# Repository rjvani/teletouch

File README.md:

# TeletouchApi

This project was generated with [angular-cli](https://github.com/angular/angular-cli) version 1.0.0-beta.28.3.

## Development server
Run `ng serve` for a dev server. Navigate to `http://localhost:4200/`. The app will automatically reload if you change any of the source files.

## Code scaffolding

Run `ng generate component component-name` to generate a new component. You can also use `ng generate directive/pipe/service/class/module`.

## Build

Run `ng build` to build the project. The build artifacts will be stored in the `dist/` directory. Use the `-prod` flag for a production build.

## Running unit tests

Run `ng test` to execute the unit tests via [Karma](https://karma-runner.github.io).

## Running end-to-end tests

Run `ng e2e` to execute the end-to-end tests via [Protractor](http://www.protractortest.org/).
Before running the tests make sure you are serving the app via `ng serve`.

## Deploying to GitHub Pages

Run `ng github-pages:deploy` to deploy to GitHub Pages.

## Further help

To get more help on the `angular-cli` use `ng help` or go check out the [Angular-CLI README](https://github.com/angular/angular-cli/blob/master/README.md).

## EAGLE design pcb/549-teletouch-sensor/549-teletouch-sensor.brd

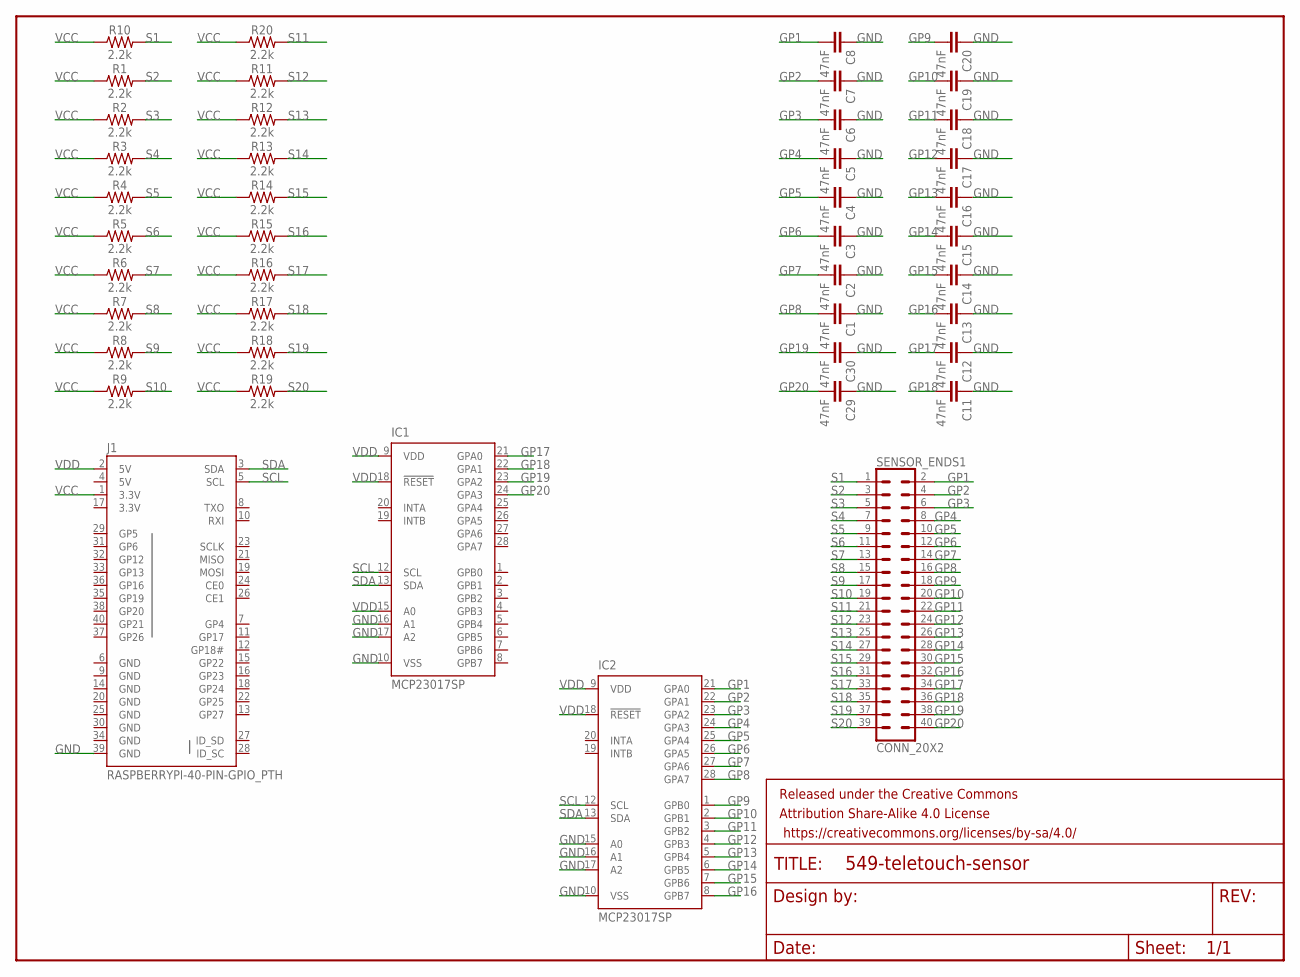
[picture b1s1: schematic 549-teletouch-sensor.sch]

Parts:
C1, C2, C3, C4, C5, C6, C7, C8, C11, C12, C13, C14, C15, C16, C17, C18, C19, C20, C29, C30: 47nF; 0603
FRAME1: FRAME-LETTER; CREATIVE_COMMONS
IC1, IC2: MCP23017SP; DIL28-3
J1: RASPBERRYPI-40-PIN-GPIO_PTH; 2X20_SHROUDED
R1, R2, R3, R4, R5, R6, R7, R8, R9, R10, R11, R12, R13, R14, R15, R16, R17, R18, R19, R20: 2.2k; 0603
SENSOR_ENDS1: CONN_20X2; 2X20

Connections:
3.3V: J1.17 (3.3V)
5V: J1.4 (5V)
GND: C1.1, C2.1, C3.1, C4.1, C5.1, C6.1, C7.1, C8.1, C11.1, C12.1, C13.1, C14.1, C15.1, C16.1, C17.1, C18.1, C19.1, C20.1, C29.1, C30.1, IC1.10 (VSS), IC1.16 (A1), IC1.17 (A2), IC2.10 (VSS), IC2.15 (A0), IC2.16 (A1), IC2.17 (A2), J1.6 (GND), J1.9 (GND), J1.14 (GND), J1.20 (GND), J1.25 (GND), J1.30 (GND), J1.34 (GND), J1.39 (GND)
GP1: C8.2, IC2.21 (GPA0), SENSOR_ENDS1.2
GP2: C7.2, IC2.22 (GPA1), SENSOR_ENDS1.4
GP3: C6.2, IC2.23 (GPA2), SENSOR_ENDS1.6
GP4: C5.2, IC2.24 (GPA3), SENSOR_ENDS1.8
GP5: C4.2, IC2.25 (GPA4), SENSOR_ENDS1.10
GP6: C3.2, IC2.26 (GPA5), SENSOR_ENDS1.12
GP7: C2.2, IC2.27 (GPA6), SENSOR_ENDS1.14
GP8: C1.2, IC2.28 (GPA7), SENSOR_ENDS1.16
GP9: C20.2, IC2.1 (GPB0), SENSOR_ENDS1.18
GP10: C19.2, IC2.2 (GPB1), SENSOR_ENDS1.20
GP11: C18.2, IC2.3 (GPB2), SENSOR_ENDS1.22
GP12: C17.2, IC2.4 (GPB3), SENSOR_ENDS1.24
GP13: C16.2, IC2.5 (GPB4), SENSOR_ENDS1.26
GP14: C15.2, IC2.6 (GPB5), SENSOR_ENDS1.28
GP15: C14.2, IC2.7 (GPB6), SENSOR_ENDS1.30
GP16: C13.2, IC2.8 (GPB7), SENSOR_ENDS1.32
GP17: C12.2, IC1.21 (GPA0), SENSOR_ENDS1.34
GP18: C11.2, IC1.22 (GPA1), SENSOR_ENDS1.36
GP19: C30.2, IC1.23 (GPA2), SENSOR_ENDS1.38
GP20: C29.2, IC1.24 (GPA3), SENSOR_ENDS1.40
S1: R10.2, SENSOR_ENDS1.1
S2: R1.2, SENSOR_ENDS1.3
S3: R2.2, SENSOR_ENDS1.5
S4: R3.2, SENSOR_ENDS1.7
S5: R4.2, SENSOR_ENDS1.9
S6: R5.2, SENSOR_ENDS1.11
S7: R6.2, SENSOR_ENDS1.13
S8: R7.2, SENSOR_ENDS1.15
S9: R8.2, SENSOR_ENDS1.17
S10: R9.2, SENSOR_ENDS1.19
S11: R20.2, SENSOR_ENDS1.21
S12: R11.2, SENSOR_ENDS1.23
S13: R12.2, SENSOR_ENDS1.25
S14: R13.2, SENSOR_ENDS1.27
S15: R14.2, SENSOR_ENDS1.29
S16: R15.2, SENSOR_ENDS1.31
S17: R16.2, SENSOR_ENDS1.33
S18: R17.2, SENSOR_ENDS1.35
S19: R18.2, SENSOR_ENDS1.37
S20: R19.2, SENSOR_ENDS1.39
SCL: IC1.12 (SCL), IC2.12 (SCL), J1.5 (SCL)
SDA: IC1.13 (SDA), IC2.13 (SDA), J1.3 (SDA)
VCC: J1.1 (3.3V), R1.1, R2.1, R3.1, R4.1, R5.1, R6.1, R7.1, R8.1, R9.1, R10.1, R11.1, R12.1, R13.1, R14.1, R15.1, R16.1, R17.1, R18.1, R19.1, R20.1
VDD: IC1.9 (VDD), IC1.15 (A0), IC1.18 (!RESET), IC2.9 (VDD), IC2.18 (!RESET), J1.2 (5V)

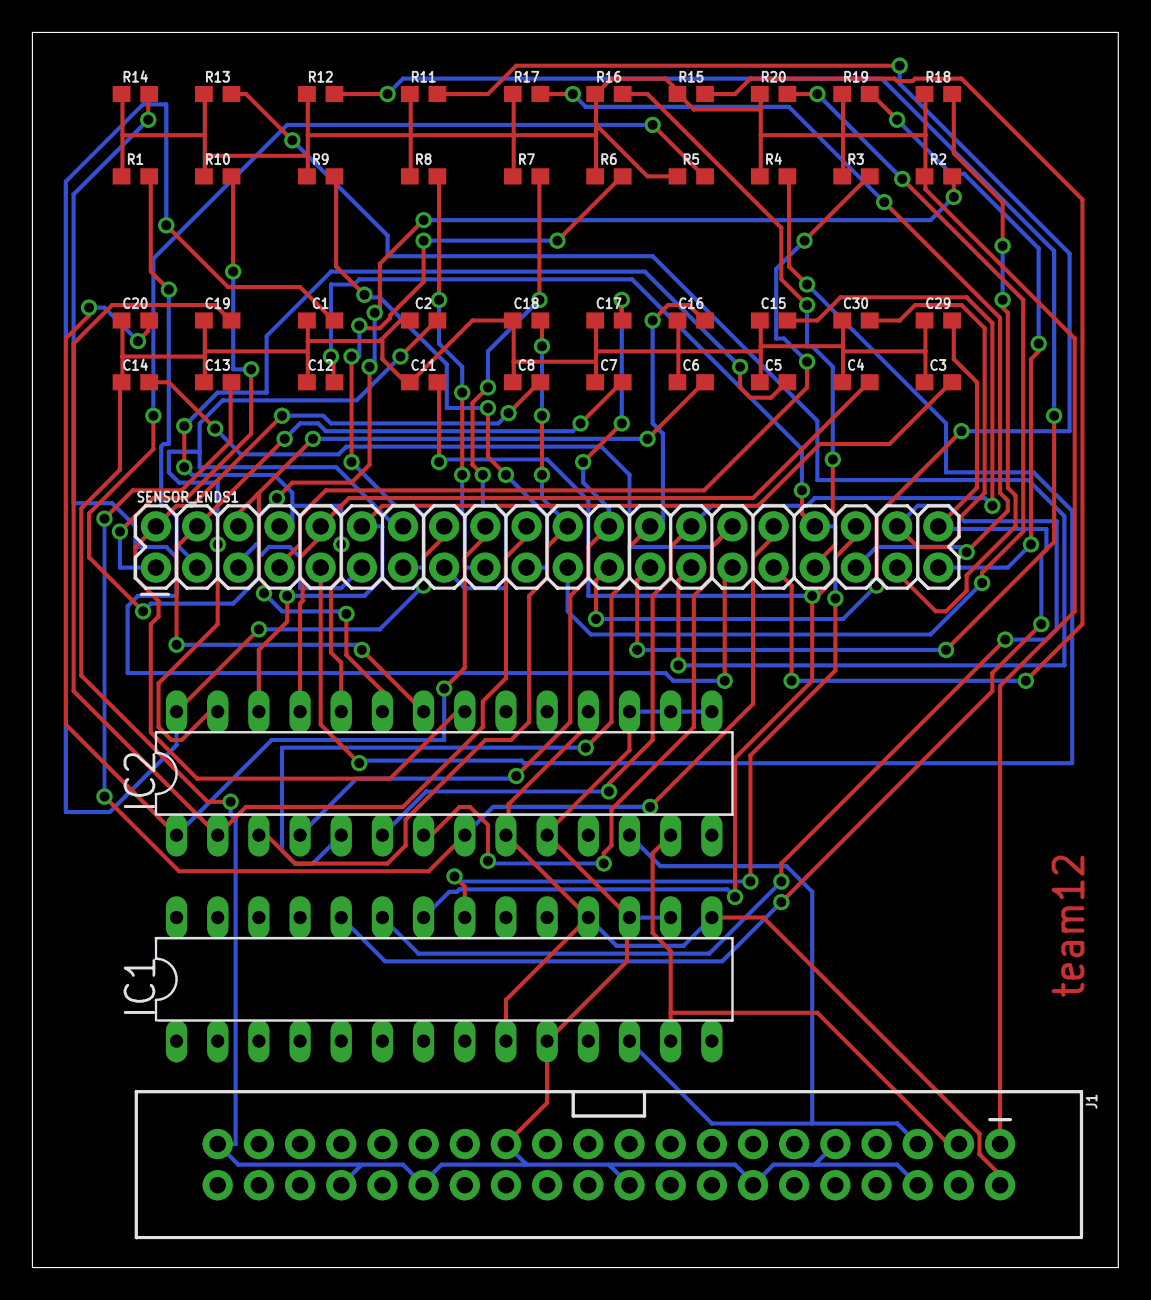
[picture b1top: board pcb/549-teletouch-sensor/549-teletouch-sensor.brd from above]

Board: 2 copper layers, 67.0 x 76.2 mm, 45 parts (0 on the bottom side), 45 nets.

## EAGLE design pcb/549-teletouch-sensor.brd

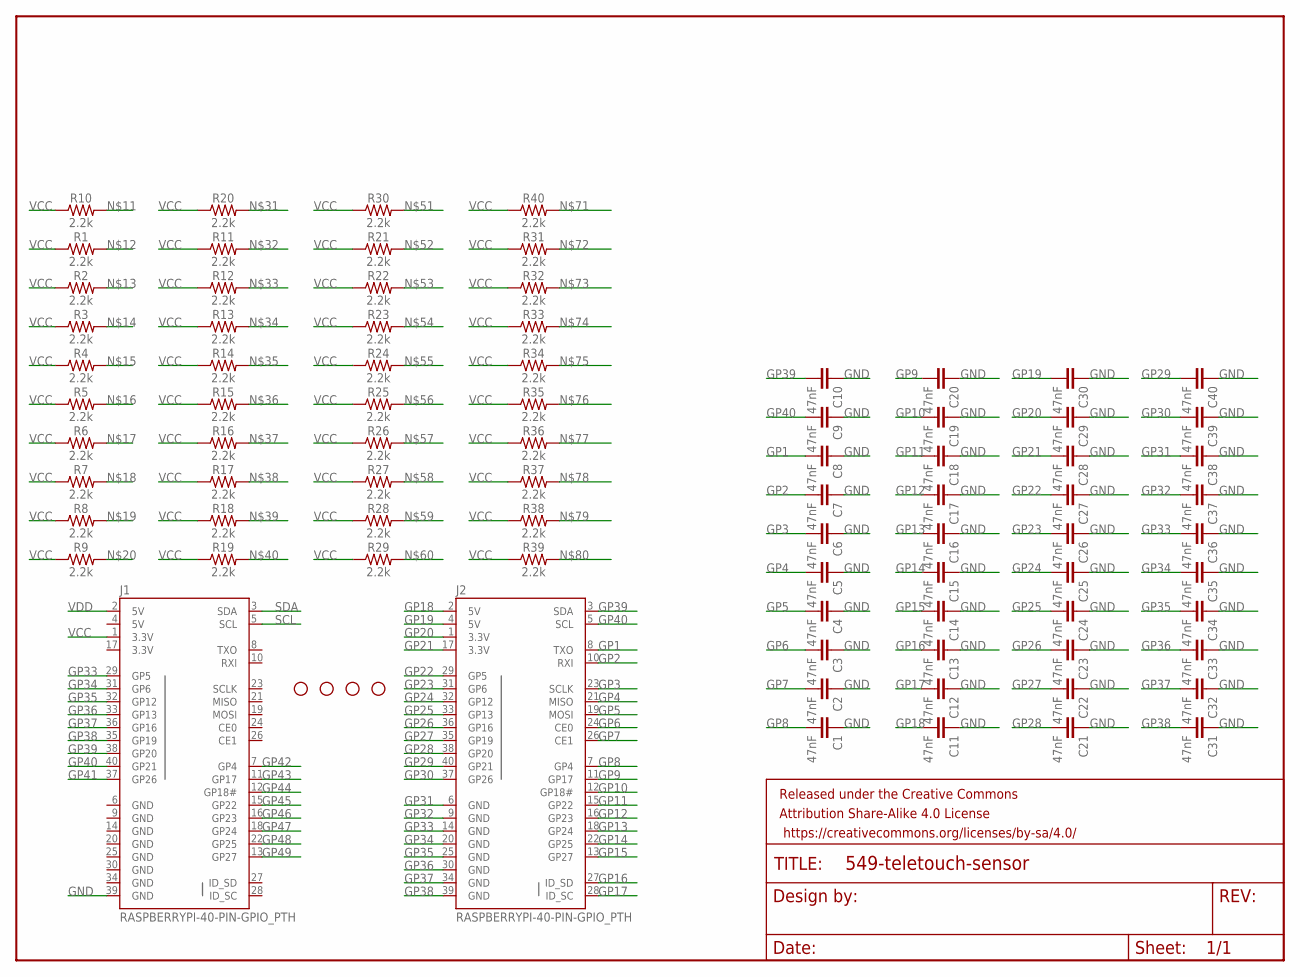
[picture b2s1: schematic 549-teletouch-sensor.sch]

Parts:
C1, C2, C3, C4, C5, C6, C7, C8, C9, C10, C11, C12, C13, C14, C15, C16, C17, C18, C19, C20, C21, C22, C23, C24, C25, C26, C27, C28, C29, C30, C31, C32, C33, C34, C35, C36, C37, C38, C39, C40: 47nF; 0603
FRAME1: FRAME-LETTER; CREATIVE_COMMONS
H1, H2, H3, H4: STAND-OFF
J1, J2: RASPBERRYPI-40-PIN-GPIO_PTH; 2X20_SHROUDED
R1, R2, R3, R4, R5, R6, R7, R8, R9, R10, R11, R12, R13, R14, R15, R16, R17, R18, R19, R20, R21, R22, R23, R24, R25, R26, R27, R28, R29, R30, R31, R32, R33, R34, R35, R36, R37, R38, R39, R40: 2.2k; 0603

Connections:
3.3V: J1.17 (3.3V)
5V: J1.4 (5V)
GND: C1.1, C2.1, C3.1, C4.1, C5.1, C6.1, C7.1, C8.1, C9.1, C10.1, C11.1, C12.1, C13.1, C14.1, C15.1, C16.1, C17.1, C18.1, C19.1, C20.1, C21.1, C22.1, C23.1, C24.1, C25.1, C26.1, C27.1, C28.1, C29.1, C30.1, C31.1, C32.1, C33.1, C34.1, C35.1, C36.1, C37.1, C38.1, C39.1, C40.1, J1.6 (GND), J1.9 (GND), J1.14 (GND), J1.20 (GND), J1.25 (GND), J1.30 (GND), J1.34 (GND), J1.39 (GND)
GP1: C8.2, J2.8 (TXO)
GP2: C7.2, J2.10 (RXI)
GP3: C6.2, J2.23 (SCLK)
GP4: C5.2, J2.21 (MISO)
GP5: C4.2, J2.19 (MOSI)
GP6: C3.2, J2.24 (CE0)
GP7: C2.2, J2.26 (CE1)
GP8: C1.2, J2.7 (GP4)
GP9: C20.2, J2.11 (GP17)
GP10: C19.2, J2.12 (GP18#)
GP11: C18.2, J2.15 (GP22)
GP12: C17.2, J2.16 (GP23)
GP13: C16.2, J2.18 (GP24)
GP14: C15.2, J2.22 (GP25)
GP15: C14.2, J2.13 (GP27)
GP16: C13.2, J2.27 (ID_SD)
GP17: C12.2, J2.28 (ID_SC)
GP18: C11.2, J2.2 (5V)
GP19: C30.2, J2.4 (5V)
GP20: C29.2, J2.1 (3.3V)
GP21: C28.2, J2.17 (3.3V)
GP22: C27.2, J2.29 (GP5)
GP23: C26.2, J2.31 (GP6)
GP24: C25.2, J2.32 (GP12)
GP25: C24.2, J2.33 (GP13)
GP26: C23.2, J2.36 (GP16)
GP27: C22.2, J2.35 (GP19)
GP28: C21.2, J2.38 (GP20)
GP29: C40.2, J2.40 (GP21)
GP30: C39.2, J2.37 (GP26)
GP31: C38.2, J2.6 (GND)
GP32: C37.2, J2.9 (GND)
GP33: C36.2, J1.29 (GP5), J2.14 (GND)
GP34: C35.2, J1.31 (GP6), J2.20 (GND)
GP35: C34.2, J1.32 (GP12), J2.25 (GND)
GP36: C33.2, J1.33 (GP13), J2.30 (GND)
GP37: C32.2, J1.36 (GP16), J2.34 (GND)
GP38: C31.2, J1.35 (GP19), J2.39 (GND)
GP39: C10.2, J1.38 (GP20), J2.3 (SDA)
GP40: C9.2, J1.40 (GP21), J2.5 (SCL)
GP41: J1.37 (GP26)
GP42: J1.7 (GP4)
GP43: J1.11 (GP17)
GP44: J1.12 (GP18#)
GP45: J1.15 (GP22)
GP46: J1.16 (GP23)
GP47: J1.18 (GP24)
GP48: J1.22 (GP25)
GP49: J1.13 (GP27)
SCL: J1.5 (SCL)
SDA: J1.3 (SDA)
VCC: J1.1 (3.3V), R1.1, R2.1, R3.1, R4.1, R5.1, R6.1, R7.1, R8.1, R9.1, R10.1, R11.1, R12.1, R13.1, R14.1, R15.1, R16.1, R17.1, R18.1, R19.1, R20.1, R21.1, R22.1, R23.1, R24.1, R25.1, R26.1, R27.1, R28.1, R29.1, R30.1, R31.1, R32.1, R33.1, R34.1, R35.1, R36.1, R37.1, R38.1, R39.1, R40.1
VDD: J1.2 (5V)

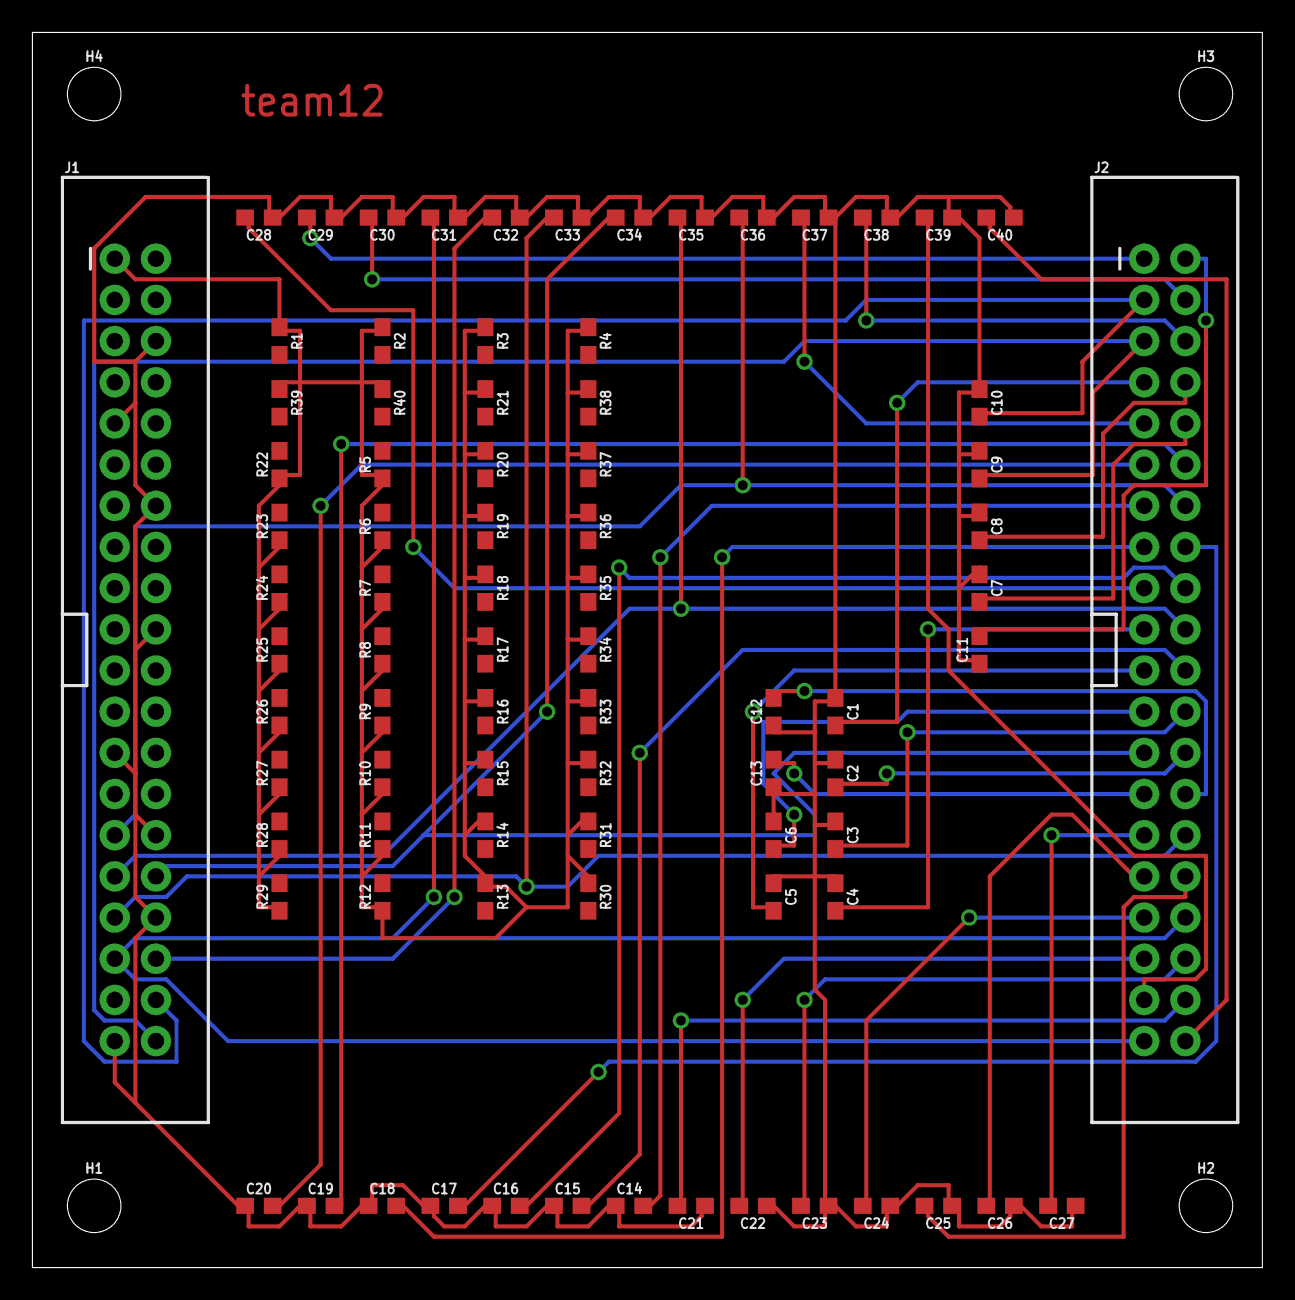
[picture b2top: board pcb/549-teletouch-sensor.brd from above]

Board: 2 copper layers, 75.9 x 76.2 mm, 87 parts (0 on the bottom side), 42 nets.

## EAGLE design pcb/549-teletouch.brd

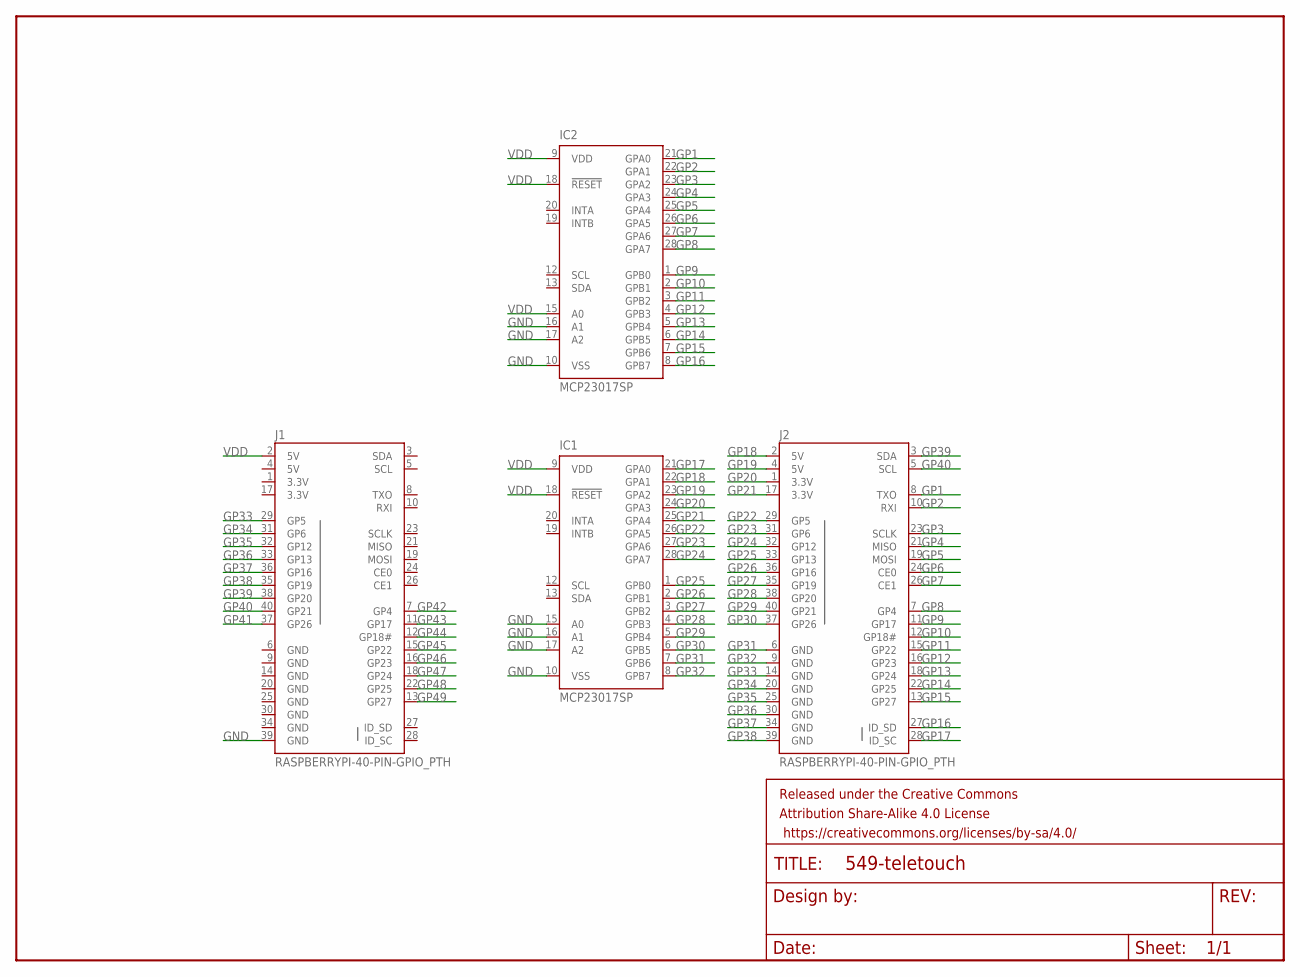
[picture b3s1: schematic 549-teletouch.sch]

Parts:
FRAME1: FRAME-LETTER; CREATIVE_COMMONS
IC1, IC2: MCP23017SP; DIL28-3
J1, J2: RASPBERRYPI-40-PIN-GPIO_PTH; 2X20_SHROUDED

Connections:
3.3V: J1.1 (3.3V), J1.17 (3.3V)
5V: J1.4 (5V)
GND: IC1.10 (VSS), IC1.15 (A0), IC1.16 (A1), IC1.17 (A2), IC2.10 (VSS), IC2.16 (A1), IC2.17 (A2), J1.6 (GND), J1.9 (GND), J1.14 (GND), J1.20 (GND), J1.25 (GND), J1.30 (GND), J1.34 (GND), J1.39 (GND)
GP1: IC2.21 (GPA0), J2.8 (TXO)
GP2: IC2.22 (GPA1), J2.10 (RXI)
GP3: IC2.23 (GPA2), J2.23 (SCLK)
GP4: IC2.24 (GPA3), J2.21 (MISO)
GP5: IC2.25 (GPA4), J2.19 (MOSI)
GP6: IC2.26 (GPA5), J2.24 (CE0)
GP7: IC2.27 (GPA6), J2.26 (CE1)
GP8: IC2.28 (GPA7), J2.7 (GP4)
GP9: IC2.1 (GPB0), J2.11 (GP17)
GP10: IC2.2 (GPB1), J2.12 (GP18#)
GP11: IC2.3 (GPB2), J2.15 (GP22)
GP12: IC2.4 (GPB3), J2.16 (GP23)
GP13: IC2.5 (GPB4), J2.18 (GP24)
GP14: IC2.6 (GPB5), J2.22 (GP25)
GP15: IC2.7 (GPB6), J2.13 (GP27)
GP16: IC2.8 (GPB7), J2.27 (ID_SD)
GP17: IC1.21 (GPA0), J2.28 (ID_SC)
GP18: IC1.22 (GPA1), J2.2 (5V)
GP19: IC1.23 (GPA2), J2.4 (5V)
GP20: IC1.24 (GPA3), J2.1 (3.3V)
GP21: IC1.25 (GPA4), J2.17 (3.3V)
GP22: IC1.26 (GPA5), J2.29 (GP5)
GP23: IC1.27 (GPA6), J2.31 (GP6)
GP24: IC1.28 (GPA7), J2.32 (GP12)
GP25: IC1.1 (GPB0), J2.33 (GP13)
GP26: IC1.2 (GPB1), J2.36 (GP16)
GP27: IC1.3 (GPB2), J2.35 (GP19)
GP28: IC1.4 (GPB3), J2.38 (GP20)
GP29: IC1.5 (GPB4), J2.40 (GP21)
GP30: IC1.6 (GPB5), J2.37 (GP26)
GP31: IC1.7 (GPB6), J2.6 (GND)
GP32: IC1.8 (GPB7), J2.9 (GND)
GP33: J1.29 (GP5), J2.14 (GND)
GP34: J1.31 (GP6), J2.20 (GND)
GP35: J1.32 (GP12), J2.25 (GND)
GP36: J1.33 (GP13), J2.30 (GND)
GP37: J1.36 (GP16), J2.34 (GND)
GP38: J1.35 (GP19), J2.39 (GND)
GP39: J1.38 (GP20), J2.3 (SDA)
GP40: J1.40 (GP21), J2.5 (SCL)
GP41: J1.37 (GP26)
GP42: J1.7 (GP4)
GP43: J1.11 (GP17)
GP44: J1.12 (GP18#)
GP45: J1.15 (GP22)
GP46: J1.16 (GP23)
GP47: J1.18 (GP24)
GP48: J1.22 (GP25)
GP49: J1.13 (GP27)
SCL: IC1.12 (SCL), IC2.12 (SCL), J1.5 (SCL)
SDA: IC1.13 (SDA), IC2.13 (SDA), J1.3 (SDA)
VDD: IC1.9 (VDD), IC1.18 (!RESET), IC2.9 (VDD), IC2.15 (A0), IC2.18 (!RESET), J1.2 (5V)

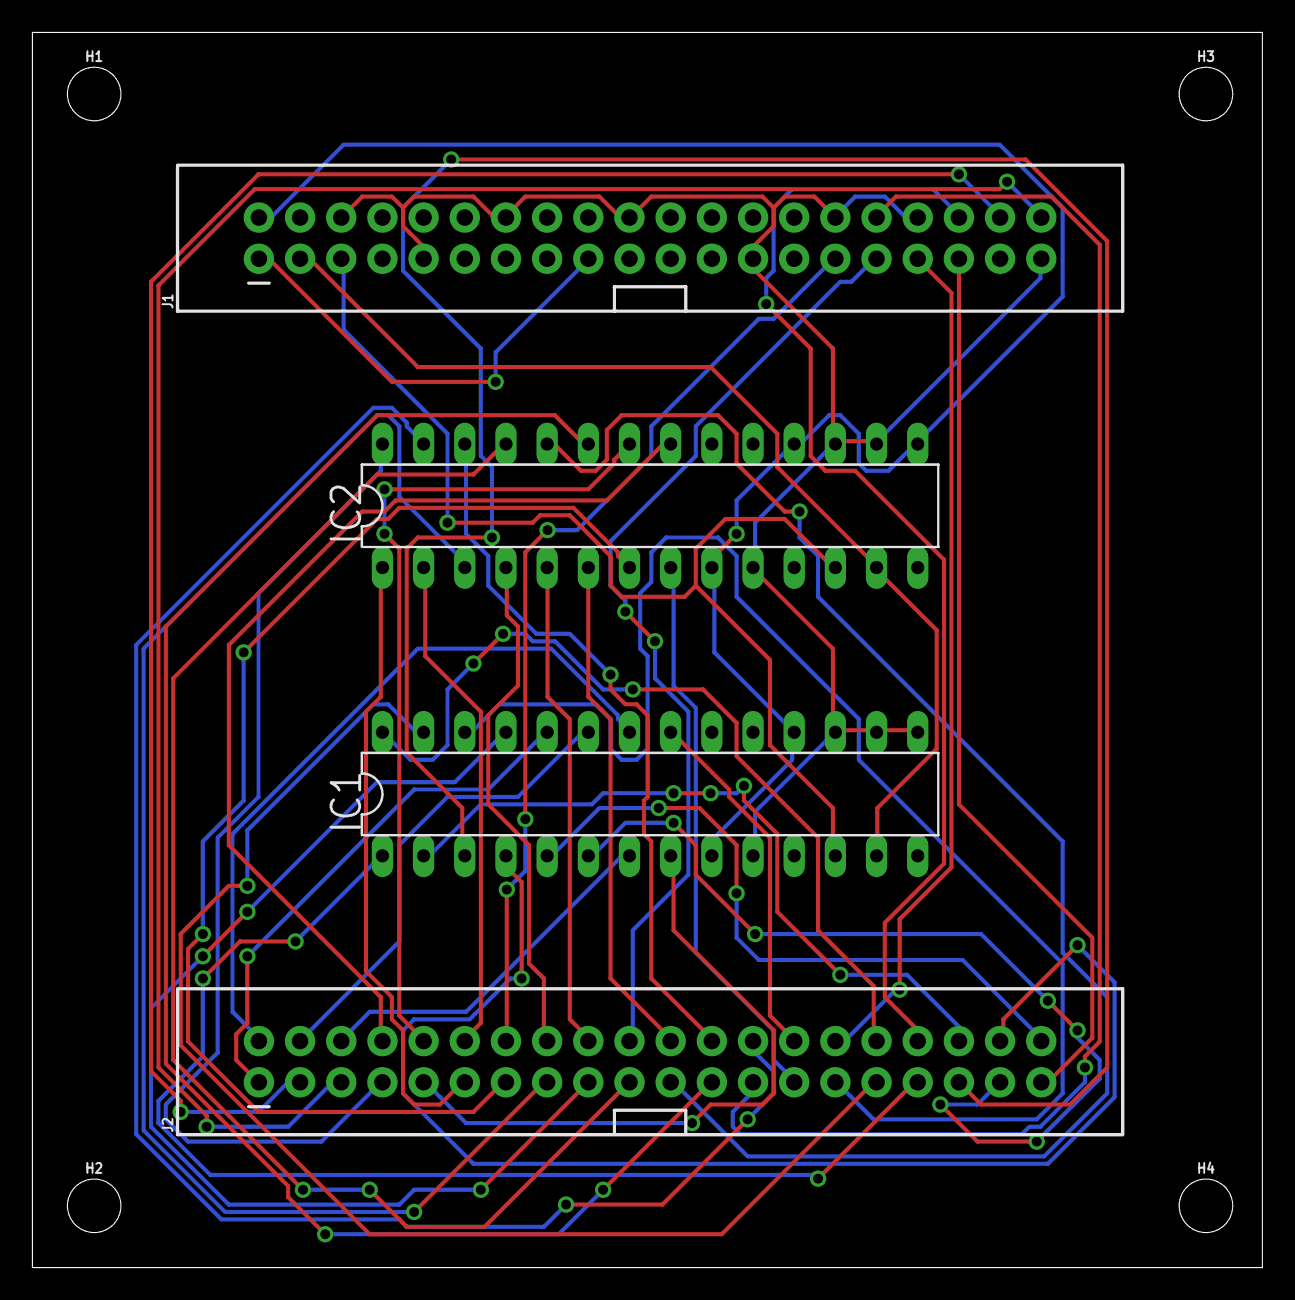
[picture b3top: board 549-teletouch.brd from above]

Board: 2 copper layers, 75.9 x 76.2 mm, 9 parts (0 on the bottom side), 45 nets.

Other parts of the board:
H1, H2, H3, H4: STAND-OFF

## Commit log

2017-03-03 trivial
2017-03-20 Add README.
2017-03-20 Add initial schematic for headers / expanders.
2017-03-21 Add initial board.
2017-03-21 Add auto-routed version.
2017-03-22 Update SDA / SCL connections in schematic and board.
2017-03-26 python code for wifi send and receive
2017-03-26 switch actuators
2017-03-26 Added notes
2017-03-26 Added wifi notes
2017-03-26 demo code for switching actuators over wifi
2017-03-29 Create gerber files.
2017-04-02 ui code and updated ip addresses
2017-04-02 typo
2017-04-02 sender
2017-04-02 switch directory
2017-04-02 hello
2017-04-02 no inputs to stop
2017-04-03 beautiful presets
2017-04-03 Update .gitignore with DS_Store.
2017-04-05 Update receiver code to only respond to changes.
2017-04-05 Add timerFired for sender code.
2017-04-05 add sensor reading code in sender
2017-04-05 sensor fabric
2017-04-05 expander demo working
2017-04-05 ui is cancer
2017-04-05 Update receiver code.
2017-04-06 update pin map
2017-04-06 testing expander
2017-04-09 add notes on measuring resistance with rasppi
2017-04-09 Update receiver code to handle sensor input.
2017-04-10 Update sender code.
2017-04-11 added sensor pcb
2017-04-11 adding Gerber files
2017-04-11 reorganize EAGLE files for both PCBs
2017-04-14 clean up and read sensor vals from expander
2017-04-14 sensor working with expander
2017-04-14 rm from wrong dir
2017-04-16 updated sensor pcb
2017-04-17 updated to half the amount of sensors
2017-04-18 add name and clean up
2017-04-18 Temporary push
2017-04-18 Temp commit
2017-04-18 fixed calibrations
2017-04-18 sender code fixed
2017-04-25 pcb updates
2017-04-25 added prelim calibration, cleaned up send.py
2017-05-04 heroku
2017-05-04 add server
2017-05-04 add api
2017-05-04 actually make express
2017-05-04 fix port issue
2017-05-05 add dynamic ip grabbing
2017-05-05 add 16 lra mapping
2017-05-05 add wake endpoint
2017-05-06 add channel actuators
2017-05-06 receiver final code, add recordings
2017-05-06 fuck sadjf
2017-05-06 fix crontab pi
2017-05-06 remove requests
2017-05-06 Temp commit.
2017-05-06 Shit works.

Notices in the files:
parts and their libraries:
SparkFun-Capacitors: Licensing: Creative Commons ShareAlike 4.0 International - https://creativecommons.org/licenses/by-sa/4.0
SparkFun-Aesthetics: Released under the Creative Commons Attribution Share-Alike 4.0 License
SparkFun-Aesthetics: https://creativecommons.org/licenses/by-sa/4.0
